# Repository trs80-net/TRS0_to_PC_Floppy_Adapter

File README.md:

# TRS0_to_PC_Floppy_Adapter

An adapter to connect 'modern' floppies to TRS-80 1,2,3,4,12, & 16 machines.

PCB files are complete.  BOARD HAS NOT BEEN TESTED YET.

***I NEED TESTERS! If you will test, I'll send you a free board.***

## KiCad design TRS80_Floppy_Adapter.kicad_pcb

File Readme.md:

An adapter to connect 'modern' floppies to TRS-80 1,2,3,4,12, & 16 machines.

PCB files are complete. BOARD HAS NOT BEEN TESTED YET.

***I NEED TESTERS! If you will test, I'll send you a free board.***

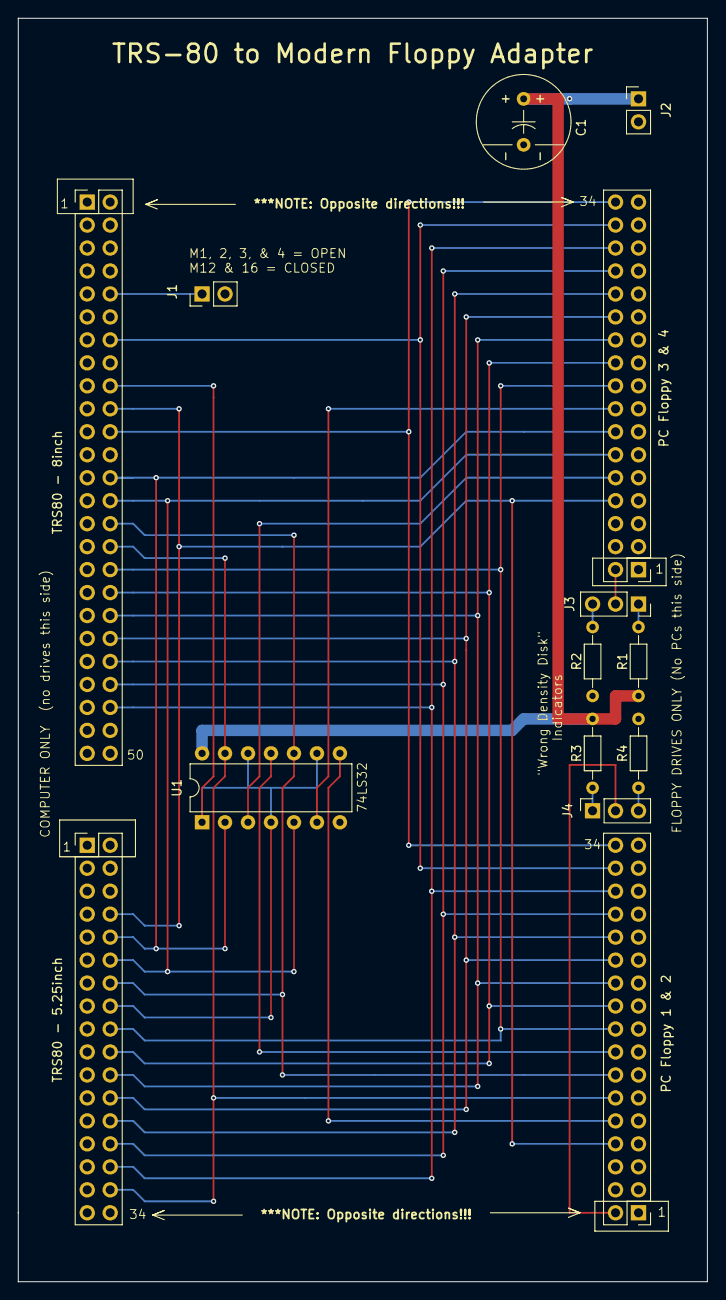
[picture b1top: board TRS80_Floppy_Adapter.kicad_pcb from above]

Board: 2 copper layers, 76.2 x 139.7 mm, 14 parts (0 on the bottom side), 28 nets.

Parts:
C1: Capacitor; Capcitor Radial .200
J1, J2: Conn_02x01; PinHeader_1x02_P2.54mm_Vertical
J3, J4: Conn_01x03_Socket; PinSocket_1x03_P2.54mm_Vertical
PC Floppy 1 & 2, PC Floppy 3 & 4: Conn_02x17_Odd_Even; PinHeader_2x17_P2.54mm_Vertical
R1, R2, R3, R4: Resistor; R_Axial_DIN0204_L3.6mm_D1.6mm_P7.62mm_Horizontal
TRS80 - 5.25inch: Conn_02x17_Odd_Even; PinHeader_2x17_P2.54mm_Vertical
TRS80 - 8inch: Conn_02x25_Odd_Even; PinHeader_2x25_P2.54mm_Vertical
U1: 74LS32; DIP-14pin

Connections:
+5V: C1.1, J2.1, R1.2, R3.2, U1.14 (VCC)
GND: C1.2, J1.2, J2.2, PC Floppy 1 & 2.1, PC Floppy 1 & 2.3, PC Floppy 1 & 2.5, PC Floppy 1 & 2.7, PC Floppy 1 & 2.9, PC Floppy 1 & 2.11, PC Floppy 1 & 2.13, PC Floppy 1 & 2.15, PC Floppy 1 & 2.17, PC Floppy 1 & 2.19, PC Floppy 1 & 2.21, PC Floppy 1 & 2.23, PC Floppy 1 & 2.25, PC Floppy 1 & 2.27, PC Floppy 1 & 2.29, PC Floppy 1 & 2.31, PC Floppy 1 & 2.33, PC Floppy 3 & 4.1, PC Floppy 3 & 4.3, PC Floppy 3 & 4.5, PC Floppy 3 & 4.7, PC Floppy 3 & 4.9, PC Floppy 3 & 4.11, PC Floppy 3 & 4.13, PC Floppy 3 & 4.15, PC Floppy 3 & 4.17, PC Floppy 3 & 4.19, PC Floppy 3 & 4.21, PC Floppy 3 & 4.23, PC Floppy 3 & 4.25, PC Floppy 3 & 4.27, PC Floppy 3 & 4.29, PC Floppy 3 & 4.31, PC Floppy 3 & 4.33, R2.2, R4.2, TRS80 - 5.25inch.1, TRS80 - 5.25inch.3, TRS80 - 5.25inch.5, TRS80 - 5.25inch.7, TRS80 - 5.25inch.9, TRS80 - 5.25inch.11, TRS80 - 5.25inch.13, TRS80 - 5.25inch.15, TRS80 - 5.25inch.17, TRS80 - 5.25inch.19, TRS80 - 5.25inch.21, TRS80 - 5.25inch.23, TRS80 - 5.25inch.25, TRS80 - 5.25inch.27, TRS80 - 5.25inch.29, TRS80 - 5.25inch.31, TRS80 - 5.25inch.33, TRS80 - 8inch.1, TRS80 - 8inch.3, TRS80 - 8inch.5, TRS80 - 8inch.7, TRS80 - 8inch.9, TRS80 - 8inch.11, TRS80 - 8inch.13, TRS80 - 8inch.15, TRS80 - 8inch.17, TRS80 - 8inch.19, TRS80 - 8inch.21, TRS80 - 8inch.23, TRS80 - 8inch.25, TRS80 - 8inch.27, TRS80 - 8inch.29, TRS80 - 8inch.31, TRS80 - 8inch.33, TRS80 - 8inch.35, TRS80 - 8inch.37, TRS80 - 8inch.39, TRS80 - 8inch.41, TRS80 - 8inch.43, TRS80 - 8inch.45, TRS80 - 8inch.47, TRS80 - 8inch.49, U1.7 (GND)
unnamed: J1.1, TRS80 - 8inch.10
unnamed: J3.1, R1.1
unnamed: J3.2, PC Floppy 3 & 4.2
unnamed: J3.3, R2.1
unnamed: J4.1, R3.1
unnamed: J4.2, PC Floppy 1 & 2.2
unnamed: J4.3, R4.1
unnamed: PC Floppy 1 & 2.8, PC Floppy 3 & 4.8, TRS80 - 5.25inch.8, TRS80 - 8inch.20
unnamed: PC Floppy 1 & 2.10, U1.8
unnamed: PC Floppy 1 & 2.12, TRS80 - 5.25inch.32, TRS80 - 8inch.32, U1.13
unnamed: PC Floppy 1 & 2.14, TRS80 - 5.25inch.14, TRS80 - 8inch.30, U1.10
unnamed: PC Floppy 1 & 2.16, U1.11
unnamed: PC Floppy 1 & 2.18, PC Floppy 3 & 4.18, TRS80 - 5.25inch.18, TRS80 - 8inch.34
unnamed: PC Floppy 1 & 2.20, PC Floppy 3 & 4.20, TRS80 - 5.25inch.20, TRS80 - 8inch.36
unnamed: PC Floppy 1 & 2.22, PC Floppy 3 & 4.22, TRS80 - 5.25inch.22, TRS80 - 8inch.38
unnamed: PC Floppy 1 & 2.24, PC Floppy 3 & 4.24, TRS80 - 5.25inch.24, TRS80 - 8inch.40
unnamed: PC Floppy 1 & 2.26, PC Floppy 3 & 4.26, TRS80 - 5.25inch.26, TRS80 - 8inch.42
unnamed: PC Floppy 1 & 2.28, PC Floppy 3 & 4.28, TRS80 - 5.25inch.28, TRS80 - 8inch.44
unnamed: PC Floppy 1 & 2.30, PC Floppy 3 & 4.30, TRS80 - 5.25inch.30, TRS80 - 8inch.46
unnamed: PC Floppy 1 & 2.32, PC Floppy 3 & 4.32, TRS80 - 8inch.14
unnamed: PC Floppy 1 & 2.34, PC Floppy 3 & 4.34, TRS80 - 8inch.22
unnamed: PC Floppy 3 & 4.10, U1.3
unnamed: PC Floppy 3 & 4.12, TRS80 - 5.25inch.12, TRS80 - 8inch.28, U1.5
unnamed: PC Floppy 3 & 4.14, TRS80 - 5.25inch.10, TRS80 - 8inch.26, U1.2
unnamed: PC Floppy 3 & 4.16, U1.6
unnamed: TRS80 - 5.25inch.16, TRS80 - 8inch.18, U1.1, U1.4, U1.9, U1.12
